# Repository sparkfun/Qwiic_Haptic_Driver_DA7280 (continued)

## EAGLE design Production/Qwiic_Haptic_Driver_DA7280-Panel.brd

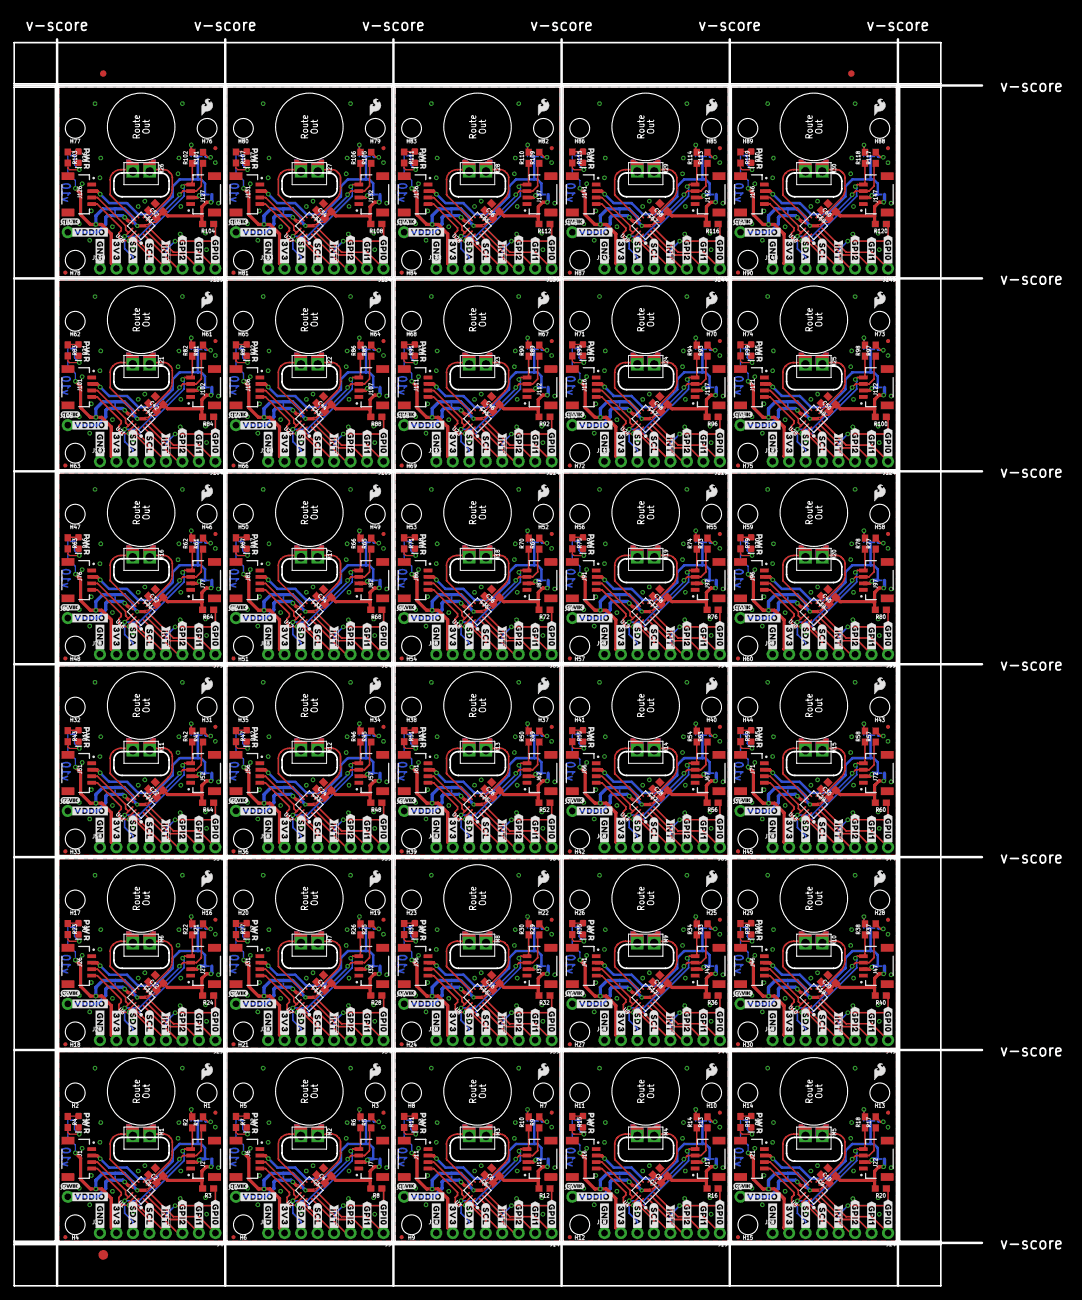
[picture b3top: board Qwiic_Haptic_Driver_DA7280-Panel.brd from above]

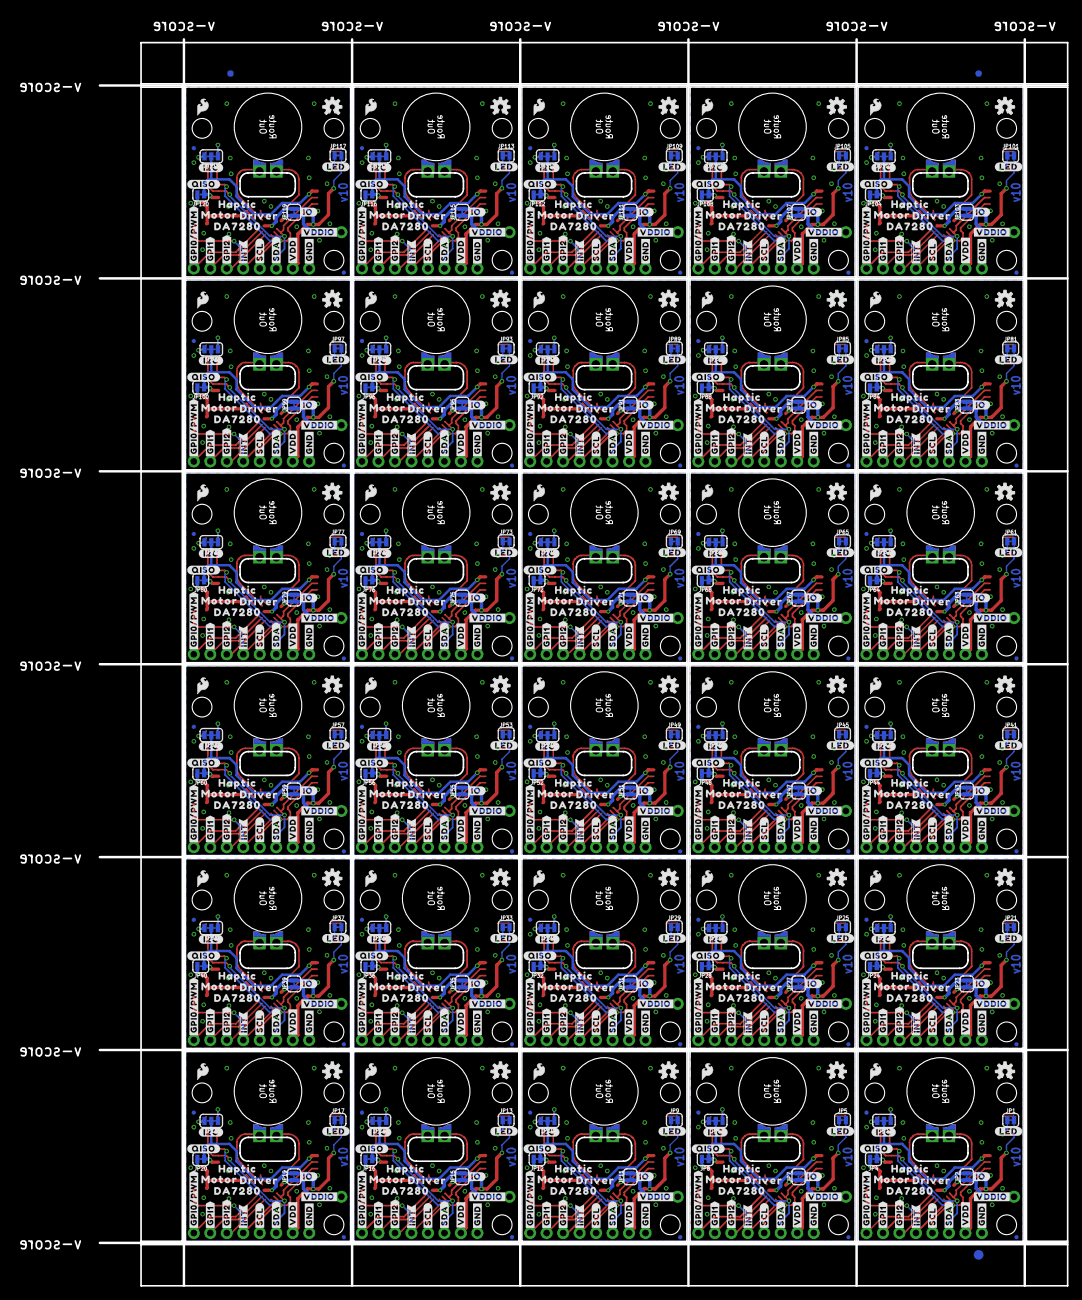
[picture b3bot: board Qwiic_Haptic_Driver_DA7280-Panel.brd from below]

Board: 2 copper layers, 162.3 x 195.9 mm, 1686 parts (753 on the bottom side), 480 nets.

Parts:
C1, C3, C5, C7, C9, C11, C13, C15, C17, C19, C21, C23, C25, C27, C29, C31, C33, C35, C37, C39, C41, C43, C45, C47, C49, C51, C53, C55, C57, C59: 0.1uF; 0603
C2, C4, C6, C8, C10, C12, C14, C16, C18, C20, C22, C24, C26, C28, C30, C32, C34, C36, C38, C40, C42, C44, C46, C48, C50, C52, C54, C56, C58, C60: 4.7uF; 0603
D1, D2, D3, D4, D5, D6, D7, D8, D9, D10, D11, D12, D13, D14, D15, D16, D17, D18, D19, D20, D21, D22, D23, D24, D25, D26, D27, D28, D29, D30: RED; LED-0603
E$1, E$2, E$3, E$4: FIDUCIAL-1X2
E$5, E$6: FIDUCIAL-1.5X3
FD1, FD2, FD3, FD4, FD5, FD6, FD7, FD8, FD9, FD10, FD11, FD12, FD13, FD14, FD15, FD16, FD17, FD18, FD19, FD20, FD21, FD22, FD23, FD24, FD25, FD26, FD27, FD28, FD29, FD30, FD31, FD32, FD33, FD34, FD35, FD36, FD37, FD38, FD39, FD40, FD41, FD42, FD43, FD44, FD45, FD46, FD47, FD48, FD49, FD50, FD51, FD52, FD53, FD54, FD55, FD56, FD57, FD58, FD59, FD60, FD61, FD62, FD63, FD64, FD65, FD66, FD67, FD68, FD69, FD70, FD71, FD72, FD73, FD74, FD75, FD76, FD77, FD78, FD79, FD80, FD81, FD82, FD83, FD84, FD85, FD86, FD87, FD88, FD89, FD90, FD91, FD92, FD93, FD94, FD95, FD96, FD97, FD98, FD99, FD100, FD101, FD102, FD103, FD104, FD105, FD106, FD107, FD108, FD109, FD110, FD111, FD112, FD113, FD114, FD115, FD116, FD117, FD118, FD119, FD120: FIDUCIALUFIDUCIAL; FIDUCIAL-MICRO
H1, H2, H3, H4, H5, H6, H7, H8, H9, H10, H11, H12, H13, H14, H15, H16, H17, H18, H19, H20, H21, H22, H23, H24, H25, H26, H27, H28, H29, H30, H31, H32, H33, H34, H35, H36, H37, H38, H39, H40, H41, H42, H43, H44, H45, H46, H47, H48, H49, H50, H51, H52, H53, H54, H55, H56, H57, H58, H59, H60, H61, H62, H63, H64, H65, H66, H67, H68, H69, H70, H71, H72, H73, H74, H75, H76, H77, H78, H79, H80, H81, H82, H83, H84, H85, H86, H87, H88, H89, H90: STAND-OFFTIGHT; STAND-OFF-TIGHT
J1, J2, J6, J7, J11, J12, J16, J17, J21, J22, J26, J27, J31, J32, J36, J37, J41, J42, J46, J47, J51, J52, J56, J57, J61, J62, J66, J67, J71, J72, J76, J77, J81, J82, J86, J87, J91, J92, J96, J97, J101, J102, J106, J107, J111, J112, J116, J117, J121, J122, J126, J127, J131, J132, J136, J137, J141, J142, J146, J147: QWIIC_RIGHT_ANGLE; JST04_1MM_RA
J3, J4, J8, J9, J13, J14, J18, J19, J23, J24, J28, J29, J33, J34, J38, J39, J43, J44, J48, J49, J53, J54, J58, J59, J63, J64, J68, J69, J73, J74, J78, J79, J83, J84, J88, J89, J93, J94, J98, J99, J103, J104, J108, J109, J113, J114, J118, J119, J123, J124, J128, J129, J133, J134, J138, J139, J143, J144, J148, J149: 1X04_NO_SILK
J5, J10, J15, J20, J25, J30, J35, J40, J45, J50, J55, J60, J65, J70, J75, J80, J85, J90, J95, J100, J105, J110, J115, J120, J125, J130, J135, J140, J145, J150: 1X01_NO_SILK
JP1, JP2, JP4, JP5, JP7, JP8, JP9, JP11, JP12, JP13, JP15, JP16, JP17, JP19, JP20, JP21, JP23, JP24, JP25, JP27, JP28, JP29, JP31, JP32, JP33, JP35, JP36, JP37, JP39, JP40, JP41, JP43, JP44, JP45, JP47, JP48, JP49, JP51, JP52, JP53, JP55, JP56, JP57, JP59, JP60, JP61, JP63, JP64, JP65, JP67, JP68, JP69, JP71, JP72, JP73, JP75, JP76, JP77, JP79, JP80, JP81, JP83, JP84, JP85, JP87, JP88, JP89, JP91, JP92, JP93, JP95, JP96, JP97, JP99, JP100, JP101, JP103, JP104, JP105, JP107, JP108, JP109, JP111, JP112, JP113, JP115, JP116, JP117, JP119, JP120: LED; SMT-JUMPER_2_NC_TRACE_SILK
JP3, JP6, JP10, JP14, JP18, JP22, JP26, JP30, JP34, JP38, JP42, JP46, JP50, JP54, JP58, JP62, JP66, JP70, JP74, JP78, JP82, JP86, JP90, JP94, JP98, JP102, JP106, JP110, JP114, JP118: I2C_PU; SMT-JUMPER_3_2-NC_TRACE_SILK
LOGO1, LOGO2, LOGO5, LOGO7, LOGO9, LOGO11, LOGO13, LOGO15, LOGO17, LOGO19, LOGO21, LOGO23, LOGO25, LOGO27, LOGO29, LOGO31, LOGO33, LOGO35, LOGO37, LOGO39, LOGO41, LOGO43, LOGO45, LOGO47, LOGO49, LOGO51, LOGO53, LOGO55, LOGO57, LOGO59: OSHW-LOGOS; OSHW-LOGO-S
LOGO3, LOGO4, LOGO6, LOGO8, LOGO10, LOGO12, LOGO14, LOGO16, LOGO18, LOGO20, LOGO22, LOGO24, LOGO26, LOGO28, LOGO30, LOGO32, LOGO34, LOGO36, LOGO38, LOGO40, LOGO42, LOGO44, LOGO46, LOGO48, LOGO50, LOGO52, LOGO54, LOGO56, LOGO58, LOGO60: SFE_LOGO_FLAME.1_INCH; SFE_LOGO_FLAME_.1
M1, M2, M3, M4, M5, M6, M7, M8, M9, M10, M11, M12, M13, M14, M15, M16, M17, M18, M19, M20, M21, M22, M23, M24, M25, M26, M27, M28, M29, M30: G1040003D_LRA_CASTELLATED; COIN_VIBRATION_MOTOR_CASTEL
R1, R2, R5, R6, R9, R10, R13, R14, R17, R18, R21, R22, R25, R26, R29, R30, R33, R34, R37, R38, R41, R42, R45, R46, R49, R50, R53, R54, R57, R58, R61, R62, R65, R66, R69, R70, R73, R74, R77, R78, R81, R82, R85, R86, R89, R90, R93, R94, R97, R98, R101, R102, R105, R106, R109, R110, R113, R114, R117, R118: 4.7k; 0603
R3, R8, R12, R16, R20, R24, R28, R32, R36, R40, R44, R48, R52, R56, R60, R64, R68, R72, R76, R80, R84, R88, R92, R96, R100, R104, R108, R112, R116, R120: 10k; 0603
R4, R7, R11, R15, R19, R23, R27, R31, R35, R39, R43, R47, R51, R55, R59, R63, R67, R71, R75, R79, R83, R87, R91, R95, R99, R103, R107, R111, R115, R119: 1k; 0603
U1, U2, U3, U4, U5, U6, U7, U8, U9, U10, U11, U12, U13, U14, U15, U16, U17, U18, U19, U20, U21, U22, U23, U24, U25, U26, U27, U28, U29, U30: HAPTIC_DRIVER_DA7280; QFN_DA7280
U$1, U$17, U$59, U$88, U$117, U$146, U$175, U$204, U$233, U$262, U$291, U$320, U$349, U$378, U$407, U$436, U$465, U$494, U$523, U$552, U$581, U$610, U$639, U$668, U$697, U$726, U$755, U$784, U$813, U$842: QWIIC_LOGO_3MM; QWIIC_3MM
U$2, U$46, U$75, U$104, U$133, U$162, U$191, U$220, U$249, U$278, U$307, U$336, U$365, U$394, U$423, U$452, U$481, U$510, U$539, U$568, U$597, U$626, U$655, U$684, U$713, U$742, U$771, U$800, U$829, U$858: #3V3#1
U$3, U$18, U$22, U$40, U$60, U$69, U$89, U$98, U$118, U$127, U$147, U$156, U$176, U$185, U$205, U$214, U$234, U$243, U$263, U$272, U$292, U$301, U$321, U$330, U$350, U$359, U$379, U$388, U$408, U$417, U$437, U$446, U$466, U$475, U$495, U$504, U$524, U$533, U$553, U$562, U$582, U$591, U$611, U$620, U$640, U$649, U$669, U$678, U$698, U$707, U$727, U$736, U$756, U$765, U$785, U$794, U$814, U$823, U$843, U$852: #GND#0
U$4, U$32, U$61, U$90, U$119, U$148, U$177, U$206, U$235, U$264, U$293, U$322, U$351, U$380, U$409, U$438, U$467, U$496, U$525, U$554, U$583, U$612, U$641, U$670, U$699, U$728, U$757, U$786, U$815, U$844: #GPI0#6
U$5, U$33, U$62, U$91, U$120, U$149, U$178, U$207, U$236, U$265, U$294, U$323, U$352, U$381, U$410, U$439, U$468, U$497, U$526, U$555, U$584, U$613, U$642, U$671, U$700, U$729, U$758, U$787, U$816, U$845: #GPI1#6
U$6, U$34, U$63, U$92, U$121, U$150, U$179, U$208, U$237, U$266, U$295, U$324, U$353, U$382, U$411, U$440, U$469, U$498, U$527, U$556, U$585, U$614, U$643, U$672, U$701, U$730, U$759, U$788, U$817, U$846: #GPI2#6
U$7, U$50, U$79, U$108, U$137, U$166, U$195, U$224, U$253, U$282, U$311, U$340, U$369, U$398, U$427, U$456, U$485, U$514, U$543, U$572, U$601, U$630, U$659, U$688, U$717, U$746, U$775, U$804, U$833, U$862: #VDD#4
U$8, U$35, U$64, U$93, U$122, U$151, U$180, U$209, U$238, U$267, U$296, U$325, U$354, U$383, U$412, U$441, U$470, U$499, U$528, U$557, U$586, U$615, U$644, U$673, U$702, U$731, U$760, U$789, U$818, U$847: #SDA#4
U$9, U$53, U$82, U$111, U$140, U$169, U$198, U$227, U$256, U$285, U$314, U$343, U$372, U$401, U$430, U$459, U$488, U$517, U$546, U$575, U$604, U$633, U$662, U$691, U$720, U$749, U$778, U$807, U$836, U$865: HAPTIC6
U$10, U$54, U$83, U$112, U$141, U$170, U$199, U$228, U$257, U$286, U$315, U$344, U$373, U$402, U$431, U$460, U$489, U$518, U$547, U$576, U$605, U$634, U$663, U$692, U$721, U$750, U$779, U$808, U$837, U$866: MOTOR7
U$11, U$55, U$84, U$113, U$142, U$171, U$200, U$229, U$258, U$287, U$316, U$345, U$374, U$403, U$432, U$461, U$490, U$519, U$548, U$577, U$606, U$635, U$664, U$693, U$722, U$751, U$780, U$809, U$838, U$867: DRIVER8
U$12, U$36, U$65, U$94, U$123, U$152, U$181, U$210, U$239, U$268, U$297, U$326, U$355, U$384, U$413, U$442, U$471, U$500, U$529, U$558, U$587, U$616, U$645, U$674, U$703, U$732, U$761, U$790, U$819, U$848: #GPI0#PWM#2
U$13, U$37, U$66, U$95, U$124, U$153, U$182, U$211, U$240, U$269, U$298, U$327, U$356, U$385, U$414, U$443, U$472, U$501, U$530, U$559, U$588, U$617, U$646, U$675, U$704, U$733, U$762, U$791, U$820, U$849: #GPI1#2
U$14, U$38, U$67, U$96, U$125, U$154, U$183, U$212, U$241, U$270, U$299, U$328, U$357, U$386, U$415, U$444, U$473, U$502, U$531, U$560, U$589, U$618, U$647, U$676, U$705, U$734, U$763, U$792, U$821, U$850: #GPI2#2
U$15, U$25, U$51, U$52, U$80, U$81, U$109, U$110, U$138, U$139, U$167, U$168, U$196, U$197, U$225, U$226, U$254, U$255, U$283, U$284, U$312, U$313, U$341, U$342, U$370, U$371, U$399, U$400, U$428, U$429, U$457, U$458, U$486, U$487, U$515, U$516, U$544, U$545, U$573, U$574, U$602, U$603, U$631, U$632, U$660, U$661, U$689, U$690, U$718, U$719, U$747, U$748, U$776, U$777, U$805, U$806, U$834, U$835, U$863, U$864: #VDDIO#5
U$16, U$39, U$68, U$97, U$126, U$155, U$184, U$213, U$242, U$271, U$300, U$329, U$358, U$387, U$416, U$445, U$474, U$503, U$532, U$561, U$590, U$619, U$648, U$677, U$706, U$735, U$764, U$793, U$822, U$851: #SDA#0
U$19, U$41, U$70, U$99, U$128, U$157, U$186, U$215, U$244, U$273, U$302, U$331, U$360, U$389, U$418, U$447, U$476, U$505, U$534, U$563, U$592, U$621, U$650, U$679, U$708, U$737, U$766, U$795, U$824, U$853: #SCL#5
U$20, U$42, U$71, U$100, U$129, U$158, U$187, U$216, U$245, U$274, U$303, U$332, U$361, U$390, U$419, U$448, U$477, U$506, U$535, U$564, U$593, U$622, U$651, U$680, U$709, U$738, U$767, U$796, U$825, U$854: PWR72810
U$21, U$43, U$72, U$101, U$130, U$159, U$188, U$217, U$246, U$275, U$304, U$333, U$362, U$391, U$420, U$449, U$478, U$507, U$536, U$565, U$594, U$623, U$652, U$681, U$710, U$739, U$768, U$797, U$826, U$855: #SCL#1
U$23, U$44, U$73, U$102, U$131, U$160, U$189, U$218, U$247, U$276, U$305, U$334, U$363, U$392, U$421, U$450, U$479, U$508, U$537, U$566, U$595, U$624, U$653, U$682, U$711, U$740, U$769, U$798, U$827, U$856: #I2C#4
U$24, U$45, U$74, U$103, U$132, U$161, U$190, U$219, U$248, U$277, U$306, U$335, U$364, U$393, U$422, U$451, U$480, U$509, U$538, U$567, U$596, U$625, U$654, U$683, U$712, U$741, U$770, U$799, U$828, U$857: #LED#4
U$26, U$47, U$76, U$105, U$134, U$163, U$192, U$221, U$250, U$279, U$308, U$337, U$366, U$395, U$424, U$453, U$482, U$511, U$540, U$569, U$598, U$627, U$656, U$685, U$714, U$743, U$772, U$801, U$830, U$859: SFE_LOGO_FLAME_.1
U$27, U$48, U$77, U$106, U$135, U$164, U$193, U$222, U$251, U$280, U$309, U$338, U$367, U$396, U$425, U$454, U$483, U$512, U$541, U$570, U$599, U$628, U$657, U$686, U$715, U$744, U$773, U$802, U$831, U$860: ##INT##3
U$28, U$49, U$78, U$107, U$136, U$165, U$194, U$223, U$252, U$281, U$310, U$339, U$368, U$397, U$426, U$455, U$484, U$513, U$542, U$571, U$600, U$629, U$658, U$687, U$716, U$745, U$774, U$803, U$832, U$861: ##INT##6
U$29, U$56, U$85, U$114, U$143, U$172, U$201, U$230, U$259, U$288, U$317, U$346, U$375, U$404, U$433, U$462, U$491, U$520, U$549, U$578, U$607, U$636, U$665, U$694, U$723, U$752, U$781, U$810, U$839, U$868: DA72809
U$30, U$57, U$86, U$115, U$144, U$173, U$202, U$231, U$260, U$289, U$318, U$347, U$376, U$405, U$434, U$463, U$492, U$521, U$550, U$579, U$608, U$637, U$666, U$695, U$724, U$753, U$782, U$811, U$840, U$869: #IO#6
U$31, U$58, U$87, U$116, U$145, U$174, U$203, U$232, U$261, U$290, U$319, U$348, U$377, U$406, U$435, U$464, U$493, U$522, U$551, U$580, U$609, U$638, U$667, U$696, U$725, U$754, U$783, U$812, U$841, U$870: #QISO#0

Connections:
!INT!: J4.4, R3.1, U1.P12
!INT!1: J9.4, R8.1, U2.P12
!INT!2: J14.4, R12.1, U3.P12
!INT!3: J19.4, R16.1, U4.P12
!INT!4: J24.4, R20.1, U5.P12
!INT!5: J29.4, R24.1, U6.P12
!INT!6: J34.4, R28.1, U7.P12
!INT!7: J39.4, R32.1, U8.P12
!INT!8: J44.4, R36.1, U9.P12
!INT!9: J49.4, R40.1, U10.P12
!INT!10: J54.4, R44.1, U11.P12
!INT!11: J59.4, R48.1, U12.P12
!INT!12: J64.4, R52.1, U13.P12
!INT!13: J69.4, R56.1, U14.P12
!INT!14: J74.4, R60.1, U15.P12
!INT!15: J79.4, R64.1, U16.P12
!INT!16: J84.4, R68.1, U17.P12
!INT!17: J89.4, R72.1, U18.P12
!INT!18: J94.4, R76.1, U19.P12
!INT!19: J99.4, R80.1, U20.P12
!INT!20: J104.4, R84.1, U21.P12
!INT!21: J109.4, R88.1, U22.P12
!INT!22: J114.4, R92.1, U23.P12
!INT!23: J119.4, R96.1, U24.P12
!INT!24: J124.4, R100.1, U25.P12
!INT!25: J129.4, R104.1, U26.P12
!INT!26: J134.4, R108.1, U27.P12
!INT!27: J139.4, R112.1, U28.P12
!INT!28: J144.4, R116.1, U29.P12
!INT!29: J149.4, R120.1, U30.P12
GND: C1.2, C2.2, D1.C, J1.1, J2.1, J3.1, U1.P6, U1.P7
GND1: C3.2, C4.2, D2.C, J6.1, J7.1, J8.1, U2.P6, U2.P7
GND2: C5.2, C6.2, D3.C, J11.1, J12.1, J13.1, U3.P6, U3.P7
GND3: C7.2, C8.2, D4.C, J16.1, J17.1, J18.1, U4.P6, U4.P7
GND4: C9.2, C10.2, D5.C, J21.1, J22.1, J23.1, U5.P6, U5.P7
GND5: C11.2, C12.2, D6.C, J26.1, J27.1, J28.1, U6.P6, U6.P7
GND6: C13.2, C14.2, D7.C, J31.1, J32.1, J33.1, U7.P6, U7.P7
GND7: C15.2, C16.2, D8.C, J36.1, J37.1, J38.1, U8.P6, U8.P7
GND8: C17.2, C18.2, D9.C, J41.1, J42.1, J43.1, U9.P6, U9.P7
GND9: C19.2, C20.2, D10.C, J46.1, J47.1, J48.1, U10.P6, U10.P7
GND10: C21.2, C22.2, D11.C, J51.1, J52.1, J53.1, U11.P6, U11.P7
GND11: C23.2, C24.2, D12.C, J56.1, J57.1, J58.1, U12.P6, U12.P7
GND12: C25.2, C26.2, D13.C, J61.1, J62.1, J63.1, U13.P6, U13.P7
GND13: C27.2, C28.2, D14.C, J66.1, J67.1, J68.1, U14.P6, U14.P7
GND14: C29.2, C30.2, D15.C, J71.1, J72.1, J73.1, U15.P6, U15.P7
GND15: C31.2, C32.2, D16.C, J76.1, J77.1, J78.1, U16.P6, U16.P7
GND16: C33.2, C34.2, D17.C, J81.1, J82.1, J83.1, U17.P6, U17.P7
GND17: C35.2, C36.2, D18.C, J86.1, J87.1, J88.1, U18.P6, U18.P7
GND18: C37.2, C38.2, D19.C, J91.1, J92.1, J93.1, U19.P6, U19.P7
GND19: C39.2, C40.2, D20.C, J96.1, J97.1, J98.1, U20.P6, U20.P7
GND20: C41.2, C42.2, D21.C, J101.1, J102.1, J103.1, U21.P6, U21.P7
GND21: C43.2, C44.2, D22.C, J106.1, J107.1, J108.1, U22.P6, U22.P7
GND22: C45.2, C46.2, D23.C, J111.1, J112.1, J113.1, U23.P6, U23.P7
GND23: C47.2, C48.2, D24.C, J116.1, J117.1, J118.1, U24.P6, U24.P7
GND24: C49.2, C50.2, D25.C, J121.1, J122.1, J123.1, U25.P6, U25.P7
GND25: C51.2, C52.2, D26.C, J126.1, J127.1, J128.1, U26.P6, U26.P7
GND26: C53.2, C54.2, D27.C, J131.1, J132.1, J133.1, U27.P6, U27.P7
GND27: C55.2, C56.2, D28.C, J136.1, J137.1, J138.1, U28.P6, U28.P7
GND28: C57.2, C58.2, D29.C, J141.1, J142.1, J143.1, U29.P6, U29.P7
GND29: C59.2, C60.2, D30.C, J146.1, J147.1, J148.1, U30.P6, U30.P7
GPI0/PWM: J4.1, U1.P3
GPI0/PWM1: J9.1, U2.P3
GPI0/PWM2: J14.1, U3.P3
GPI0/PWM3: J19.1, U4.P3
GPI0/PWM4: J24.1, U5.P3
GPI0/PWM5: J29.1, U6.P3
GPI0/PWM6: J34.1, U7.P3
GPI0/PWM7: J39.1, U8.P3
GPI0/PWM8: J44.1, U9.P3
GPI0/PWM9: J49.1, U10.P3
GPI0/PWM10: J54.1, U11.P3
GPI0/PWM11: J59.1, U12.P3
GPI0/PWM12: J64.1, U13.P3
GPI0/PWM13: J69.1, U14.P3
GPI0/PWM14: J74.1, U15.P3
GPI0/PWM15: J79.1, U16.P3
GPI0/PWM16: J84.1, U17.P3
GPI0/PWM17: J89.1, U18.P3
GPI0/PWM18: J94.1, U19.P3
GPI0/PWM19: J99.1, U20.P3
GPI0/PWM20: J104.1, U21.P3
GPI0/PWM21: J109.1, U22.P3
GPI0/PWM22: J114.1, U23.P3
GPI0/PWM23: J119.1, U24.P3
GPI0/PWM24: J124.1, U25.P3
GPI0/PWM25: J129.1, U26.P3
GPI0/PWM26: J134.1, U27.P3
GPI0/PWM27: J139.1, U28.P3
GPI0/PWM28: J144.1, U29.P3
GPI0/PWM29: J149.1, U30.P3
GPI1: J4.2, U1.P2
GPI2: J4.3, U1.P1
GPI3: J9.2, U2.P2
GPI4: J9.3, U2.P1
GPI5: J14.2, U3.P2
GPI6: J14.3, U3.P1
GPI7: J19.2, U4.P2
GPI8: J19.3, U4.P1
GPI9: J24.2, U5.P2
GPI10: J24.3, U5.P1
GPI11: J29.2, U6.P2
GPI12: J29.3, U6.P1
GPI13: J34.2, U7.P2
GPI14: J34.3, U7.P1
GPI15: J39.2, U8.P2
GPI16: J39.3, U8.P1
GPI17: J44.2, U9.P2
GPI18: J44.3, U9.P1
GPI19: J49.2, U10.P2
GPI20: J49.3, U10.P1
GPI21: J54.2, U11.P2
GPI22: J54.3, U11.P1
GPI23: J59.2, U12.P2
GPI24: J59.3, U12.P1
GPI25: J64.2, U13.P2
GPI26: J64.3, U13.P1
GPI27: J69.2, U14.P2
GPI28: J69.3, U14.P1
GPI29: J74.2, U15.P2
GPI30: J74.3, U15.P1
GPI31: J79.2, U16.P2
GPI32: J79.3, U16.P1
GPI33: J84.2, U17.P2
GPI34: J84.3, U17.P1
GPI35: J89.2, U18.P2
GPI36: J89.3, U18.P1
GPI37: J94.2, U19.P2
GPI38: J94.3, U19.P1
GPI39: J99.2, U20.P2
GPI40: J99.3, U20.P1
GPI41: J104.2, U21.P2
GPI42: J104.3, U21.P1
GPI43: J109.2, U22.P2
GPI44: J109.3, U22.P1
GPI45: J114.2, U23.P2
GPI46: J114.3, U23.P1
GPI47: J119.2, U24.P2
GPI48: J119.3, U24.P1
GPI49: J124.2, U25.P2
GPI50: J124.3, U25.P1
GPI51: J129.2, U26.P2
GPI52: J129.3, U26.P1
GPI53: J134.2, U27.P2
GPI54: J134.3, U27.P1
GPI55: J139.2, U28.P2
GPI56: J139.3, U28.P1
GPI57: J144.2, U29.P2
GPI58: J144.3, U29.P1
GPI59: J149.2, U30.P2
GPI60: J149.3, U30.P1
unnamed: D1.A, R4.1
unnamed: JP1.1, R4.2
unnamed: JP3.3, R1.2
unnamed: JP3.1, R2.2
unnamed: M1.P$1, U1.P5
unnamed: M1.P$2, U1.P8
unnamed: D2.A, R7.1
unnamed: JP5.1, R7.2
unnamed: JP6.3, R5.2
unnamed: JP6.1, R6.2
unnamed: M2.P$1, U2.P5
unnamed: M2.P$2, U2.P8
unnamed: D3.A, R11.1
unnamed: JP9.1, R11.2
unnamed: JP10.3, R9.2
unnamed: JP10.1, R10.2
unnamed: M3.P$1, U3.P5
unnamed: M3.P$2, U3.P8
unnamed: D4.A, R15.1
unnamed: JP13.1, R15.2
unnamed: JP14.3, R13.2
unnamed: JP14.1, R14.2
unnamed: M4.P$1, U4.P5
unnamed: M4.P$2, U4.P8
unnamed: D5.A, R19.1
unnamed: JP17.1, R19.2
unnamed: JP18.3, R17.2
unnamed: JP18.1, R18.2
unnamed: M5.P$1, U5.P5
unnamed: M5.P$2, U5.P8
unnamed: D6.A, R23.1
unnamed: JP21.1, R23.2
unnamed: JP22.3, R21.2
unnamed: JP22.1, R22.2
unnamed: M6.P$1, U6.P5
unnamed: M6.P$2, U6.P8
unnamed: D7.A, R27.1
unnamed: JP25.1, R27.2
unnamed: JP26.3, R25.2
unnamed: JP26.1, R26.2
unnamed: M7.P$1, U7.P5
unnamed: M7.P$2, U7.P8
unnamed: D8.A, R31.1
unnamed: JP29.1, R31.2
unnamed: JP30.3, R29.2
unnamed: JP30.1, R30.2
unnamed: M8.P$1, U8.P5
unnamed: M8.P$2, U8.P8
unnamed: D9.A, R35.1
unnamed: JP33.1, R35.2
unnamed: JP34.3, R33.2
unnamed: JP34.1, R34.2
unnamed: M9.P$1, U9.P5
unnamed: M9.P$2, U9.P8
unnamed: D10.A, R39.1
unnamed: JP37.1, R39.2
unnamed: JP38.3, R37.2
unnamed: JP38.1, R38.2
unnamed: M10.P$1, U10.P5
unnamed: M10.P$2, U10.P8
unnamed: D11.A, R43.1
unnamed: JP41.1, R43.2
unnamed: JP42.3, R41.2
unnamed: JP42.1, R42.2
unnamed: M11.P$1, U11.P5
unnamed: M11.P$2, U11.P8
unnamed: D12.A, R47.1
unnamed: JP45.1, R47.2
unnamed: JP46.3, R45.2
unnamed: JP46.1, R46.2
unnamed: M12.P$1, U12.P5
unnamed: M12.P$2, U12.P8
unnamed: D13.A, R51.1
unnamed: JP49.1, R51.2
unnamed: JP50.3, R49.2
unnamed: JP50.1, R50.2
unnamed: M13.P$1, U13.P5
unnamed: M13.P$2, U13.P8
unnamed: D14.A, R55.1
unnamed: JP53.1, R55.2
unnamed: JP54.3, R53.2
unnamed: JP54.1, R54.2
unnamed: M14.P$1, U14.P5
unnamed: M14.P$2, U14.P8
unnamed: D15.A, R59.1
unnamed: JP57.1, R59.2
unnamed: JP58.3, R57.2
unnamed: JP58.1, R58.2
unnamed: M15.P$1, U15.P5
unnamed: M15.P$2, U15.P8
unnamed: D16.A, R63.1
unnamed: JP61.1, R63.2
unnamed: JP62.3, R61.2
unnamed: JP62.1, R62.2
unnamed: M16.P$1, U16.P5
unnamed: M16.P$2, U16.P8
unnamed: D17.A, R67.1
unnamed: JP65.1, R67.2
unnamed: JP66.3, R65.2
unnamed: JP66.1, R66.2
unnamed: M17.P$1, U17.P5
unnamed: M17.P$2, U17.P8
unnamed: D18.A, R71.1
unnamed: JP69.1, R71.2
unnamed: JP70.3, R69.2
unnamed: JP70.1, R70.2
unnamed: M18.P$1, U18.P5
unnamed: M18.P$2, U18.P8
unnamed: D19.A, R75.1
unnamed: JP73.1, R75.2
unnamed: JP74.3, R73.2
unnamed: JP74.1, R74.2
unnamed: M19.P$1, U19.P5
unnamed: M19.P$2, U19.P8
unnamed: D20.A, R79.1
unnamed: JP77.1, R79.2
unnamed: JP78.3, R77.2
unnamed: JP78.1, R78.2
unnamed: M20.P$1, U20.P5
unnamed: M20.P$2, U20.P8
unnamed: D21.A, R83.1
unnamed: JP81.1, R83.2
unnamed: JP82.3, R81.2
unnamed: JP82.1, R82.2
unnamed: M21.P$1, U21.P5
unnamed: M21.P$2, U21.P8
unnamed: D22.A, R87.1
unnamed: JP85.1, R87.2
unnamed: JP86.3, R85.2
unnamed: JP86.1, R86.2
unnamed: M22.P$1, U22.P5
unnamed: M22.P$2, U22.P8
unnamed: D23.A, R91.1
unnamed: JP89.1, R91.2
unnamed: JP90.3, R89.2
unnamed: JP90.1, R90.2
unnamed: M23.P$1, U23.P5
unnamed: M23.P$2, U23.P8
unnamed: D24.A, R95.1
unnamed: JP93.1, R95.2
unnamed: JP94.3, R93.2
unnamed: JP94.1, R94.2
unnamed: M24.P$1, U24.P5
unnamed: M24.P$2, U24.P8
unnamed: D25.A, R99.1
unnamed: JP97.1, R99.2
unnamed: JP98.3, R97.2
unnamed: JP98.1, R98.2
unnamed: M25.P$1, U25.P5
unnamed: M25.P$2, U25.P8
unnamed: D26.A, R103.1
unnamed: JP101.1, R103.2
unnamed: JP102.3, R101.2
unnamed: JP102.1, R102.2
unnamed: M26.P$1, U26.P5
unnamed: M26.P$2, U26.P8
unnamed: D27.A, R107.1
unnamed: JP105.1, R107.2
unnamed: JP106.3, R105.2
unnamed: JP106.1, R106.2
unnamed: M27.P$1, U27.P5
unnamed: M27.P$2, U27.P8
unnamed: D28.A, R111.1
unnamed: JP109.1, R111.2
unnamed: JP110.3, R109.2
unnamed: JP110.1, R110.2
unnamed: M28.P$1, U28.P5
unnamed: M28.P$2, U28.P8
unnamed: D29.A, R115.1
unnamed: JP113.1, R115.2
unnamed: JP114.3, R113.2
unnamed: JP114.1, R114.2
unnamed: M29.P$1, U29.P5
unnamed: M29.P$2, U29.P8
unnamed: D30.A, R119.1
unnamed: JP117.1, R119.2
unnamed: JP118.3, R117.2
unnamed: JP118.1, R118.2
unnamed: M30.P$1, U30.P5
unnamed: M30.P$2, U30.P8
QWIIC_BUS: J1.2, J2.2, JP3.2, JP4.1
QWIIC_BUS1: J6.2, J7.2, JP6.2, JP8.1
QWIIC_BUS2: J11.2, J12.2, JP10.2, JP12.1
QWIIC_BUS3: J16.2, J17.2, JP14.2, JP16.1
QWIIC_BUS4: J21.2, J22.2, JP18.2, JP20.1
QWIIC_BUS5: J26.2, J27.2, JP22.2, JP24.1
QWIIC_BUS6: J31.2, J32.2, JP26.2, JP28.1
QWIIC_BUS7: J36.2, J37.2, JP30.2, JP32.1
QWIIC_BUS8: J41.2, J42.2, JP34.2, JP36.1
QWIIC_BUS9: J46.2, J47.2, JP38.2, JP40.1
QWIIC_BUS10: J51.2, J52.2, JP42.2, JP44.1
QWIIC_BUS11: J56.2, J57.2, JP46.2, JP48.1
QWIIC_BUS12: J61.2, J62.2, JP50.2, JP52.1
QWIIC_BUS13: J66.2, J67.2, JP54.2, JP56.1
QWIIC_BUS14: J71.2, J72.2, JP58.2, JP60.1
QWIIC_BUS15: J76.2, J77.2, JP62.2, JP64.1
QWIIC_BUS16: J81.2, J82.2, JP66.2, JP68.1
QWIIC_BUS17: J86.2, J87.2, JP70.2, JP72.1
QWIIC_BUS18: J91.2, J92.2, JP74.2, JP76.1
QWIIC_BUS19: J96.2, J97.2, JP78.2, JP80.1
QWIIC_BUS20: J101.2, J102.2, JP82.2, JP84.1
QWIIC_BUS21: J106.2, J107.2, JP86.2, JP88.1
QWIIC_BUS22: J111.2, J112.2, JP90.2, JP92.1
QWIIC_BUS23: J116.2, J117.2, JP94.2, JP96.1
QWIIC_BUS24: J121.2, J122.2, JP98.2, JP100.1
QWIIC_BUS25: J126.2, J127.2, JP102.2, JP104.1
QWIIC_BUS26: J131.2, J132.2, JP106.2, JP108.1
QWIIC_BUS27: J136.2, J137.2, JP110.2, JP112.1
QWIIC_BUS28: J141.2, J142.2, JP114.2, JP116.1
QWIIC_BUS29: J146.2, J147.2, JP118.2, JP120.1
SCL: J1.4, J2.4, J3.4, R2.1, U1.P11
SCL1: J6.4, J7.4, J8.4, R6.1, U2.P11
SCL2: J11.4, J12.4, J13.4, R10.1, U3.P11
SCL3: J16.4, J17.4, J18.4, R14.1, U4.P11
SCL4: J21.4, J22.4, J23.4, R18.1, U5.P11
SCL5: J26.4, J27.4, J28.4, R22.1, U6.P11
SCL6: J31.4, J32.4, J33.4, R26.1, U7.P11
SCL7: J36.4, J37.4, J38.4, R30.1, U8.P11
SCL8: J41.4, J42.4, J43.4, R34.1, U9.P11
SCL9: J46.4, J47.4, J48.4, R38.1, U10.P11
SCL10: J51.4, J52.4, J53.4, R42.1, U11.P11
SCL11: J56.4, J57.4, J58.4, R46.1, U12.P11
SCL12: J61.4, J62.4, J63.4, R50.1, U13.P11
SCL13: J66.4, J67.4, J68.4, R54.1, U14.P11
SCL14: J71.4, J72.4, J73.4, R58.1, U15.P11
SCL15: J76.4, J77.4, J78.4, R62.1, U16.P11
SCL16: J81.4, J82.4, J83.4, R66.1, U17.P11
SCL17: J86.4, J87.4, J88.4, R70.1, U18.P11
SCL18: J91.4, J92.4, J93.4, R74.1, U19.P11
SCL19: J96.4, J97.4, J98.4, R78.1, U20.P11
SCL20: J101.4, J102.4, J103.4, R82.1, U21.P11
SCL21: J106.4, J107.4, J108.4, R86.1, U22.P11
SCL22: J111.4, J112.4, J113.4, R90.1, U23.P11
SCL23: J116.4, J117.4, J118.4, R94.1, U24.P11
SCL24: J121.4, J122.4, J123.4, R98.1, U25.P11
SCL25: J126.4, J127.4, J128.4, R102.1, U26.P11
SCL26: J131.4, J132.4, J133.4, R106.1, U27.P11
SCL27: J136.4, J137.4, J138.4, R110.1, U28.P11
SCL28: J141.4, J142.4, J143.4, R114.1, U29.P11
SCL29: J146.4, J147.4, J148.4, R118.1, U30.P11
SDA: J1.3, J2.3, J3.3, R1.1, U1.P10
SDA1: J6.3, J7.3, J8.3, R5.1, U2.P10
SDA2: J11.3, J12.3, J13.3, R9.1, U3.P10
SDA3: J16.3, J17.3, J18.3, R13.1, U4.P10
SDA4: J21.3, J22.3, J23.3, R17.1, U5.P10
SDA5: J26.3, J27.3, J28.3, R21.1, U6.P10
SDA6: J31.3, J32.3, J33.3, R25.1, U7.P10
SDA7: J36.3, J37.3, J38.3, R29.1, U8.P10
SDA8: J41.3, J42.3, J43.3, R33.1, U9.P10
SDA9: J46.3, J47.3, J48.3, R37.1, U10.P10
SDA10: J51.3, J52.3, J53.3, R41.1, U11.P10
SDA11: J56.3, J57.3, J58.3, R45.1, U12.P10
SDA12: J61.3, J62.3, J63.3, R49.1, U13.P10
SDA13: J66.3, J67.3, J68.3, R53.1, U14.P10
SDA14: J71.3, J72.3, J73.3, R57.1, U15.P10
SDA15: J76.3, J77.3, J78.3, R61.1, U16.P10
SDA16: J81.3, J82.3, J83.3, R65.1, U17.P10
SDA17: J86.3, J87.3, J88.3, R69.1, U18.P10
SDA18: J91.3, J92.3, J93.3, R73.1, U19.P10
SDA19: J96.3, J97.3, J98.3, R77.1, U20.P10
SDA20: J101.3, J102.3, J103.3, R81.1, U21.P10
SDA21: J106.3, J107.3, J108.3, R85.1, U22.P10
SDA22: J111.3, J112.3, J113.3, R89.1, U23.P10
SDA23: J116.3, J117.3, J118.3, R93.1, U24.P10
SDA24: J121.3, J122.3, J123.3, R97.1, U25.P10
SDA25: J126.3, J127.3, J128.3, R101.1, U26.P10
SDA26: J131.3, J132.3, J133.3, R105.1, U27.P10
SDA27: J136.3, J137.3, J138.3, R109.1, U28.P10
SDA28: J141.3, J142.3, J143.3, R113.1, U29.P10
SDA29: J146.3, J147.3, J148.3, R117.1, U30.P10
VDD: C1.1, C2.1, J3.2, JP1.2, JP2.2, JP4.2, R3.2, U1.P4
VDD1: C3.1, C4.1, J8.2, JP5.2, JP7.2, JP8.2, R8.2, U2.P4
VDD2: C5.1, C6.1, J13.2, JP9.2, JP11.2, JP12.2, R12.2, U3.P4
VDD3: C7.1, C8.1, J18.2, JP13.2, JP15.2, JP16.2, R16.2, U4.P4
VDD4: C9.1, C10.1, J23.2, JP17.2, JP19.2, JP20.2, R20.2, U5.P4
VDD5: C11.1, C12.1, J28.2, JP21.2, JP23.2, JP24.2, R24.2, U6.P4
VDD6: C13.1, C14.1, J33.2, JP25.2, JP27.2, JP28.2, R28.2, U7.P4
VDD7: C15.1, C16.1, J38.2, JP29.2, JP31.2, JP32.2, R32.2, U8.P4
VDD8: C17.1, C18.1, J43.2, JP33.2, JP35.2, JP36.2, R36.2, U9.P4
VDD9: C19.1, C20.1, J48.2, JP37.2, JP39.2, JP40.2, R40.2, U10.P4
VDD10: C21.1, C22.1, J53.2, JP41.2, JP43.2, JP44.2, R44.2, U11.P4
VDD11: C23.1, C24.1, J58.2, JP45.2, JP47.2, JP48.2, R48.2, U12.P4
VDD12: C25.1, C26.1, J63.2, JP49.2, JP51.2, JP52.2, R52.2, U13.P4
VDD13: C27.1, C28.1, J68.2, JP53.2, JP55.2, JP56.2, R56.2, U14.P4
VDD14: C29.1, C30.1, J73.2, JP57.2, JP59.2, JP60.2, R60.2, U15.P4
VDD15: C31.1, C32.1, J78.2, JP61.2, JP63.2, JP64.2, R64.2, U16.P4
VDD16: C33.1, C34.1, J83.2, JP65.2, JP67.2, JP68.2, R68.2, U17.P4
VDD17: C35.1, C36.1, J88.2, JP69.2, JP71.2, JP72.2, R72.2, U18.P4
VDD18: C37.1, C38.1, J93.2, JP73.2, JP75.2, JP76.2, R76.2, U19.P4
VDD19: C39.1, C40.1, J98.2, JP77.2, JP79.2, JP80.2, R80.2, U20.P4
VDD20: C41.1, C42.1, J103.2, JP81.2, JP83.2, JP84.2, R84.2, U21.P4
VDD21: C43.1, C44.1, J108.2, JP85.2, JP87.2, JP88.2, R88.2, U22.P4
VDD22: C45.1, C46.1, J113.2, JP89.2, JP91.2, JP92.2, R92.2, U23.P4
VDD23: C47.1, C48.1, J118.2, JP93.2, JP95.2, JP96.2, R96.2, U24.P4
VDD24: C49.1, C50.1, J123.2, JP97.2, JP99.2, JP100.2, R100.2, U25.P4
VDD25: C51.1, C52.1, J128.2, JP101.2, JP103.2, JP104.2, R104.2, U26.P4
VDD26: C53.1, C54.1, J133.2, JP105.2, JP107.2, JP108.2, R108.2, U27.P4
VDD27: C55.1, C56.1, J138.2, JP109.2, JP111.2, JP112.2, R112.2, U28.P4
VDD28: C57.1, C58.1, J143.2, JP113.2, JP115.2, JP116.2, R116.2, U29.P4
VDD29: C59.1, C60.1, J148.2, JP117.2, JP119.2, JP120.2, R120.2, U30.P4
VDDIO: J5.1, JP2.1, U1.P9
VDDIO1: J10.1, JP7.1, U2.P9
VDDIO2: J15.1, JP11.1, U3.P9
VDDIO3: J20.1, JP15.1, U4.P9
VDDIO4: J25.1, JP19.1, U5.P9
VDDIO5: J30.1, JP23.1, U6.P9
VDDIO6: J35.1, JP27.1, U7.P9
VDDIO7: J40.1, JP31.1, U8.P9
VDDIO8: J45.1, JP35.1, U9.P9
VDDIO9: J50.1, JP39.1, U10.P9
VDDIO10: J55.1, JP43.1, U11.P9
VDDIO11: J60.1, JP47.1, U12.P9
VDDIO12: J65.1, JP51.1, U13.P9
VDDIO13: J70.1, JP55.1, U14.P9
VDDIO14: J75.1, JP59.1, U15.P9
VDDIO15: J80.1, JP63.1, U16.P9
VDDIO16: J85.1, JP67.1, U17.P9
VDDIO17: J90.1, JP71.1, U18.P9
VDDIO18: J95.1, JP75.1, U19.P9
VDDIO19: J100.1, JP79.1, U20.P9
VDDIO20: J105.1, JP83.1, U21.P9
VDDIO21: J110.1, JP87.1, U22.P9
VDDIO22: J115.1, JP91.1, U23.P9
VDDIO23: J120.1, JP95.1, U24.P9
VDDIO24: J125.1, JP99.1, U25.P9
VDDIO25: J130.1, JP103.1, U26.P9
VDDIO26: J135.1, JP107.1, U27.P9
VDDIO27: J140.1, JP111.1, U28.P9
VDDIO28: J145.1, JP115.1, U29.P9
VDDIO29: J150.1, JP119.1, U30.P9

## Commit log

2020-11-10 Inital commit - Generic 1x1 Qwiic Board
2020-11-10 Adds Da7280 footprint and symbol to library
    * Adds relevant datasheets
2020-11-11 Cleans up the Haptic Motor Driver Footprint and Device
    * Adds coin vibration motor
2020-11-11 Fully routed the board - still needs silk
    Minor changes to the DA7280:
    * symbol size was shortened.
    * Footprint was centered at 0,0
2020-11-12 Adds silk to PTH headers, cleans up schematic
2020-11-12 Updates PTH headers to PTH headers with no PROD_ID
2020-11-12 Moves PTH interrupt closer to GND PTH hold and shifts all the GPI down.
2020-11-19 Adds new package for the vibration motor - one that will go through the PCB
    * The new package has castellated leads to the part was rotated 180 degrees to the edge of the board.
    * Fixes interrupt silk to reflect active low
2020-11-19 Updates SCL silk - updates LRA symbol by removing pin numbers
2021-02-02 Flips the LRA motor 180, extends board to be 1.15 x 1 inches, adds 4.7iF decoupling capacitor
    * Gerbers in repo are out of date
2021-02-03 Widens the power traces to .02" , rotates the GND,VCC, SDA, SCL header
2021-02-03 Approves two DRC errors
2021-02-11 Adds a jumper and plated through hole for separate VDDIO supply, adds silk for VDD
    * Changes power symbols to VDD and VDDIO in place of 3V3
2021-02-12 Fixes some hidden airwires, approves some minor DRC errors
2021-02-18 Adds Jumpers for separating VDDIO from VDD and Qwiic bus voltage from the board
    * Updates measures
    * Adds OSHW and SparkFun logo to board
    * Adds text to jumpers in the schematic
    * Updates symbol to use short legs
    * Adds VDD and VDDIO range
2021-02-18 Approves some minor DRC errors
2021-02-18 Adds second qwiic connecter to "qwiic bus" net so that the respective jumper can disconnect both
    * Adds some power symbols
2021-02-18 Updates the PROD_ID on the vibration motor
2021-02-19 Improves ground pour just a smidge, found better routing options when reviewing panel
2021-02-19 Adds new panel
2021-03-12 Removes incorrect gerbers from production file
2021-04-06 Change Folder Name
2021-04-13 Adds a soldering jig for the LRA motor
